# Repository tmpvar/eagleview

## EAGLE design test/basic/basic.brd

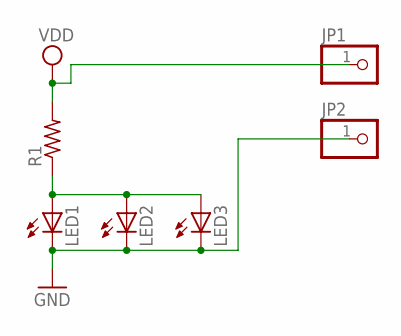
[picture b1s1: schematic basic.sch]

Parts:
JP1, JP2: PINHD-1X1; 1X01
LED1, LED2, LED3: LED5MM
R1: R-US_0204/2V; 0204V

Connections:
GND: JP2.1, LED1.K (C), LED2.K (C), LED3.K (C)
unnamed: LED1.A, LED2.A, LED3.A, R1.1
VDD: JP1.1, R1.2

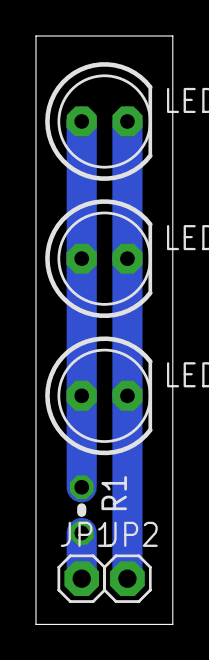
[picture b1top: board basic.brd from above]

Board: 2 copper layers, 7.6 x 32.7 mm, 6 parts (0 on the bottom side), 3 nets.

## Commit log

2014-01-19 "initial"
2014-01-19 add basic brd/sch
